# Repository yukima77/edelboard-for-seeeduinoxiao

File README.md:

# edelboard-for-seeeduinoxiao

Seeeduino XIAO用のGrove拡張基板です。

## 特長
入出力用・シリアル用・ws2812b/サーボモータ用の3つのコネクタが付いているシンプルな基板です。

Seeeduino XIAOを直付けすることによって、ピンヘッダーがあるときより薄くして使うこともできます。

ピン配置及び形状互換のAdafruit QT Pyも問題なく接続できます。

## スペック

基板サイズ（コネクタ込）：42.0×24.0×11.6 mm

## ピン

背面上部(ws2812b/サーボモータ用)：GND/VCC/P4/P5  
背面右部(シリアル用)：GND/3V3/TX(P6)/RX(P7)  
背面左部(入出力用)：GND/3V3/P1/P0

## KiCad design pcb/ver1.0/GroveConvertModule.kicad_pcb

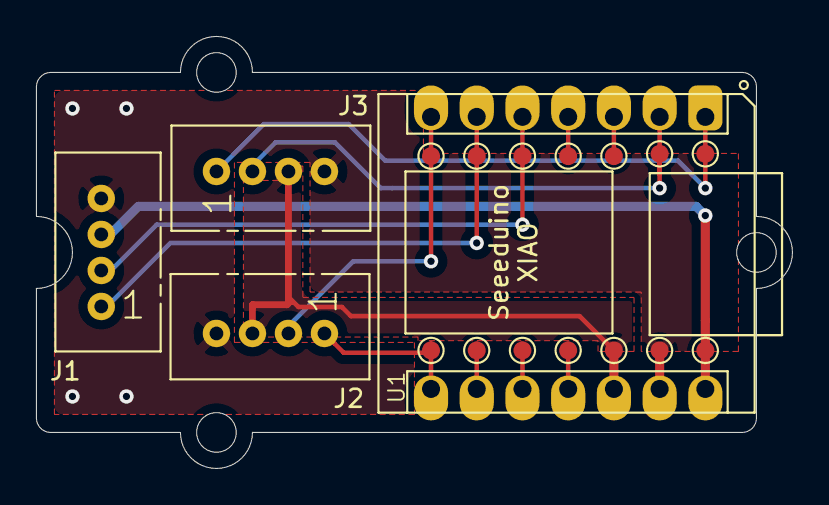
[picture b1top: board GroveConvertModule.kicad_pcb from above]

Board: 2 copper layers, 42.0 x 24.0 mm, 4 parts (0 on the bottom side), 9 nets.

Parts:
J1, J2, J3: Conn_01x04; Grove_1x04
U1: Seeeduino XIAO-MOUDLE14P-2.54-21X17.8MM_Header

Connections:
/3V3: J2.3, J3.3, U1.12
/5V: J1.3, U1.14
/A0_D0: J3.1, U1.1
/A1_D1: J3.2, U1.2
/A4_D4_SDA: J1.2, U1.5
/A5_D5_SCL: J1.1, U1.6
/A6_D6_TX: J2.2, U1.7
/A7_D7_RX: J2.1, U1.8
/GND: J1.4, J2.4, J3.4, U1.13

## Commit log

2021-05-31 Add the data of pcb.
